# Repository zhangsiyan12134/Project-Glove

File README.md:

# Project-Glove<br />
This project is to create a hand glove that capture motions to control a computer or other devices. It will increase capacity of control in VR and other computer systems. The range of motion will change from pushing buttons and triggers to active movements of the hands.

CPST Design Project <br />

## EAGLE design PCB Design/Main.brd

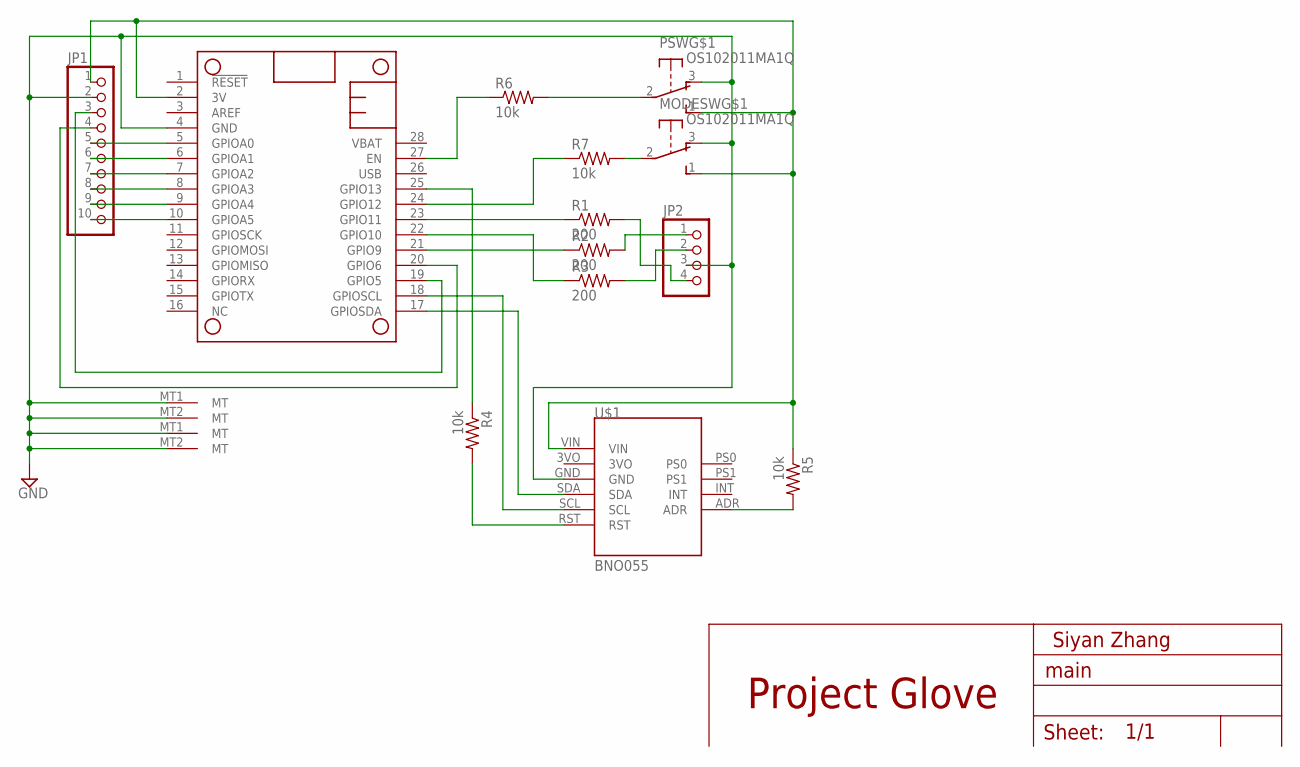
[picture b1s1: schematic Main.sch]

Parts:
JP1: PINHD-1X10; 1X10
JP2: PINHD-1X4; 1X04
MODESW: OS102011MA1Q
MS1: FEATHERWING
PSW: OS102011MA1Q
R1, R2, R3: 200; 0207/7
R4, R6, R7: 10k; 0207/7
R5: 10k; 0207/15
U$1: BNO055

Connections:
3V: JP1.1, MODESW.1 (S), MS1.2 (3V), PSW.1 (S), R5.1, U$1.VIN
GND: JP1.2, JP2.3, MODESW.3 (O), MODESW.MT1 (MT), MODESW.MT2 (MT), MS1.4 (GND), PSW.3 (O), PSW.MT1 (MT), PSW.MT2 (MT), U$1.GND
unnamed: MODESW.2, R7.2
unnamed: MS1.24 (GPIO12), R7.1
unnamed: MS1.22 (GPIO10), R3.1
unnamed: MS1.21 (GPIO9), R2.1
unnamed: MS1.23 (GPIO11), R1.1
unnamed: JP2.4, R1.2
unnamed: JP2.1, R2.2
unnamed: JP2.2, R3.2
unnamed: JP1.10, MS1.10 (GPIOA5)
unnamed: JP1.9, MS1.9 (GPIOA4)
unnamed: JP1.8, MS1.8 (GPIOA3)
unnamed: JP1.7, MS1.7 (GPIOA2)
unnamed: JP1.6, MS1.6 (GPIOA1)
unnamed: MS1.17 (GPIOSDA), U$1.SDA
unnamed: MS1.18 (GPIOSCL), U$1.SCL
unnamed: R4.2, U$1.RST
unnamed: R5.2, U$1.ADR
unnamed: MS1.25 (GPIO13), R4.1
unnamed: JP1.5, MS1.5 (GPIOA0)
unnamed: PSW.2, R6.2
unnamed: MS1.27 (EN), R6.1
unnamed: JP1.3, MS1.19 (GPIO5)
unnamed: JP1.4, MS1.20 (GPIO6)

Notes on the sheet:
Sheet:
Project Glove
Siyan Zhang

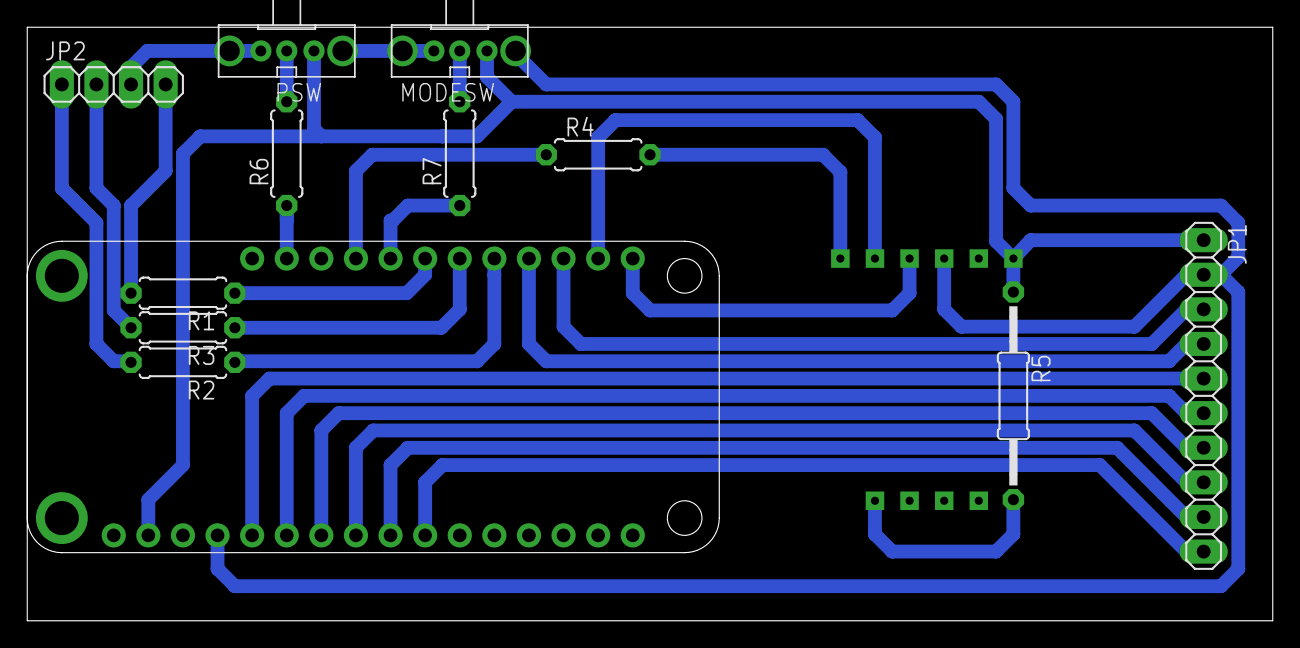
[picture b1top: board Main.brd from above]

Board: 2 copper layers, 91.4 x 43.6 mm, 14 parts (0 on the bottom side), 25 nets.

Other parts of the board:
U$2: A4L-LOC

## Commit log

2018-03-30 Rename Glove/Adafruit_BNO055.lbr to PCB Design/Adafruit_BNO055.lbr
2018-03-30 Rename Glove/Main.brd to PCB Design/Main.brd
2018-03-30 Rename Glove/Main.sch to PCB Design/Main.sch
2018-03-30 Rename Glove/eagle.epf to PCB Design/eagle.epf
2018-04-20 Update BLEmousewithIMU.ino
    Add more comments about how to calibrate the glove.
2020-11-24 Library Update
    New IMU BNO080 to replace previous BNO055
2020-11-30 CPST Design
2020-12-02 Code Reformat
2020-12-02 File revised
